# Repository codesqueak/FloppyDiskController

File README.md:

# Floppy Disk Controller Version 2.2.1

Nascom / Gemini / 80-Bus 1793 Floppy Disk Controller

## Introduction

This card has been designed to be a functional replacement for the Nascom Floppy Disk Controller.  It is fully compatible with the existing NAS-DOS software

The card is a completely new implementation of the design with a number of improvements over the original:

*	Completely new track layout
*	All components are readily available from commercial component suppliers (..and eBay!)
*	Switches are fitted to standard  DIL sockets
*	Copious test points
* Full documentation

For full documentation, see the [pdf here](FDC.pdf).

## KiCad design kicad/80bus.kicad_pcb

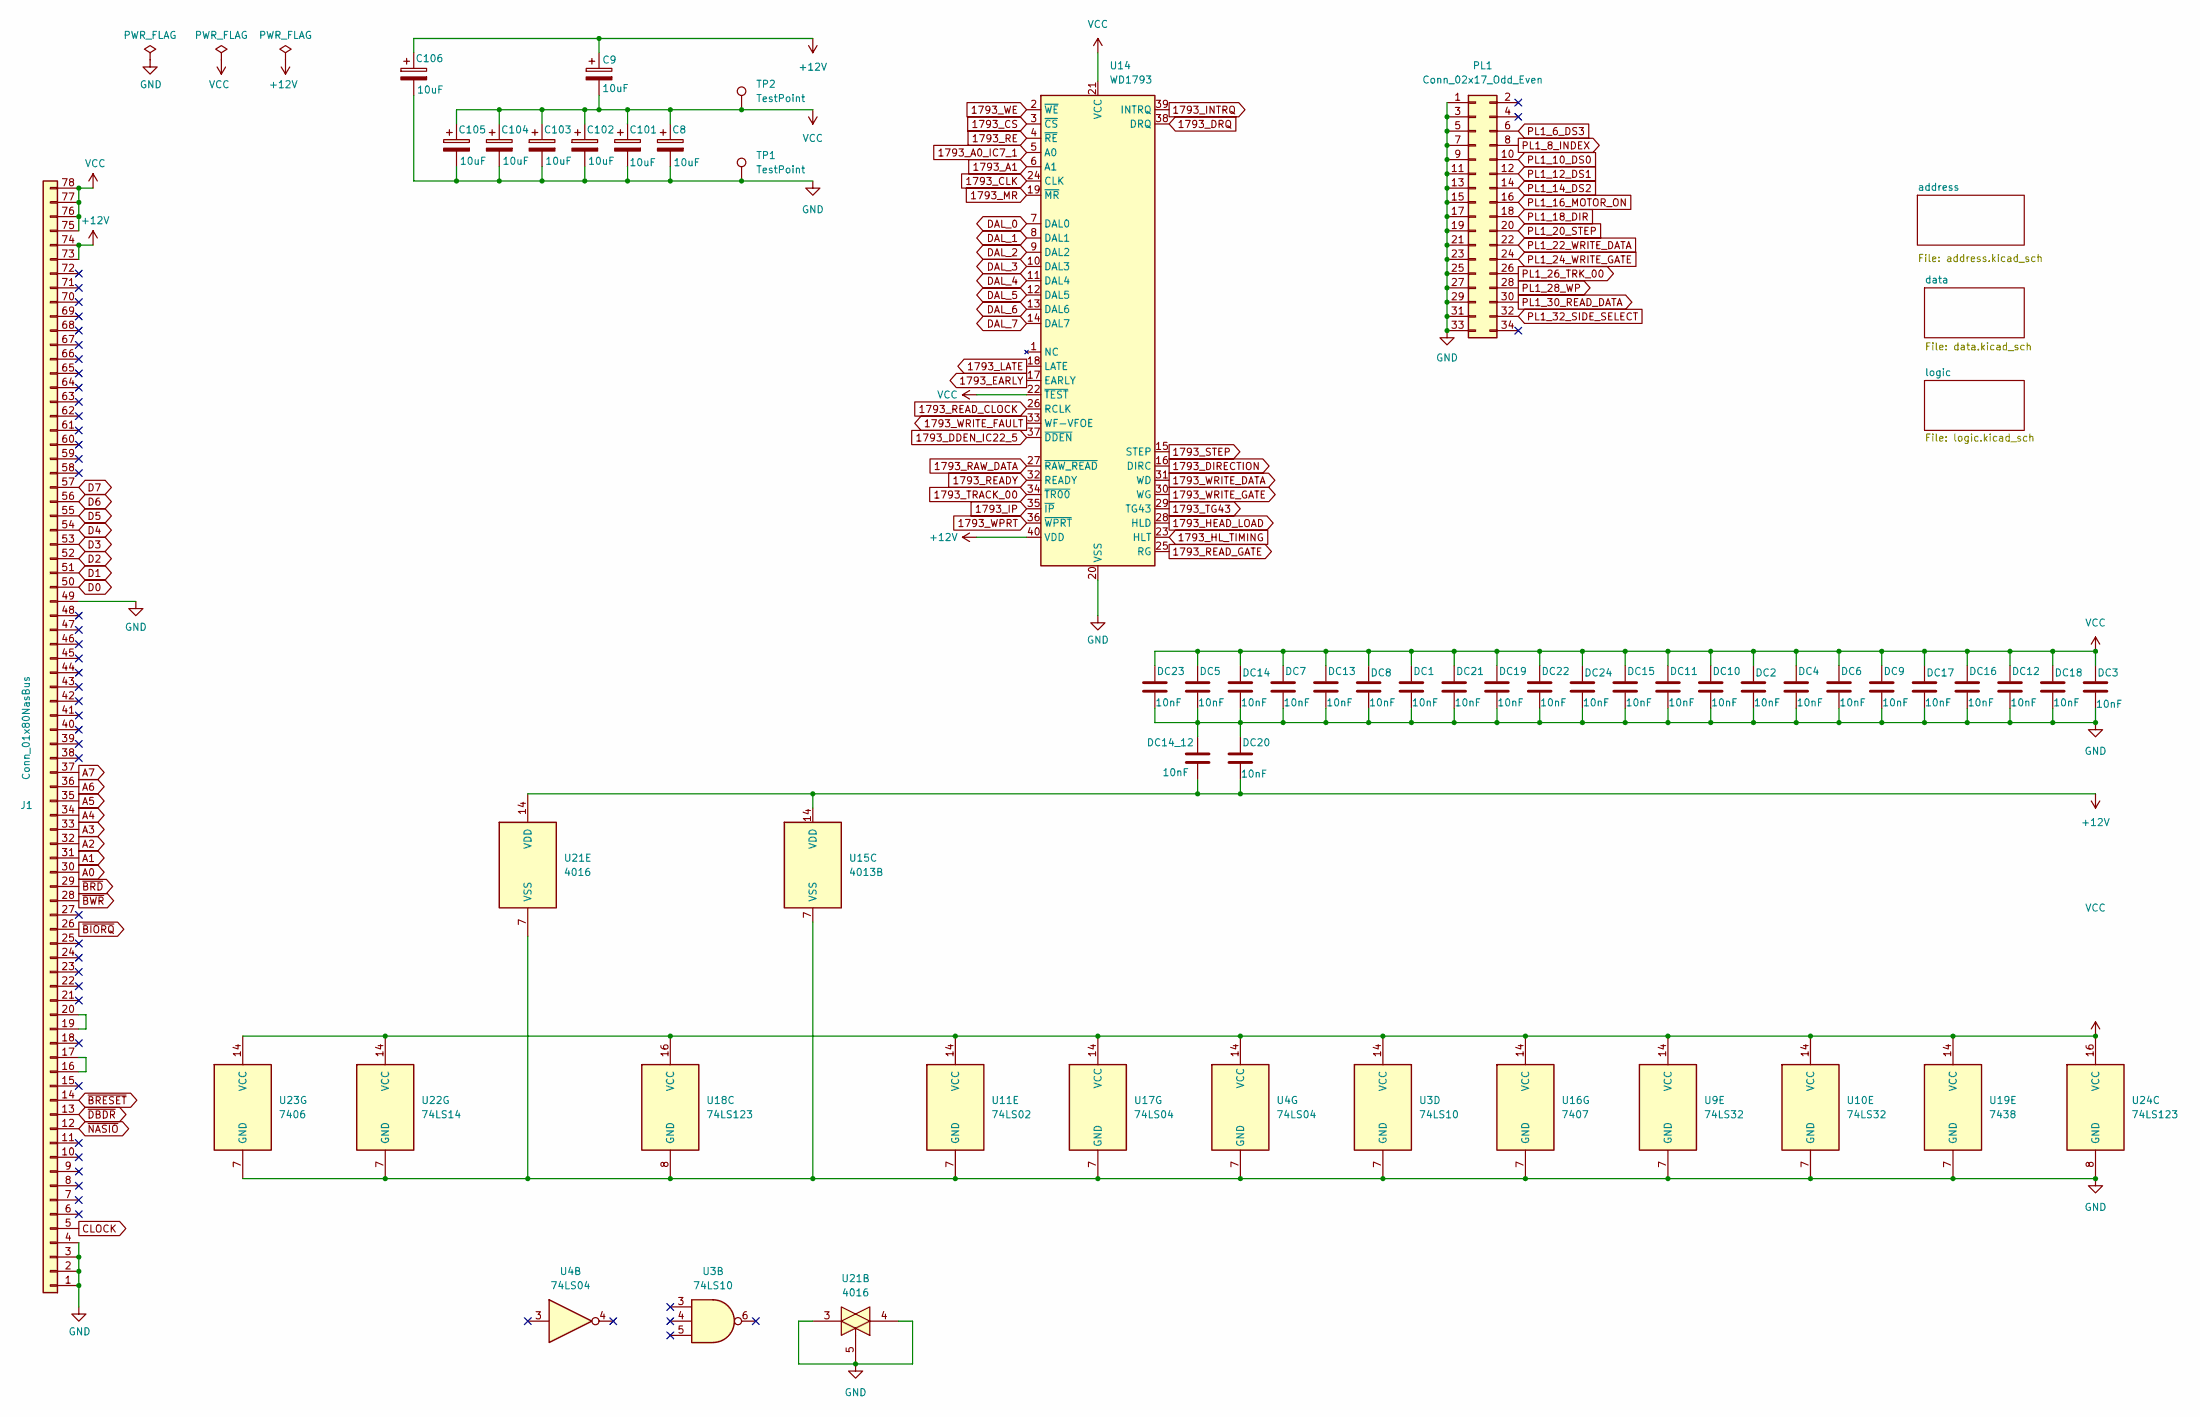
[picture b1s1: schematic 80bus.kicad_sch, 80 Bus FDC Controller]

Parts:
C8, C9, C101, C102, C103, C104, C105, C106: 10uF; C_Disc_D6.0mm_W4.4mm_P5.00mm
DC1, DC2, DC3, DC4, DC5, DC6, DC7, DC8, DC9, DC10, DC11, DC12, DC13, DC14, DC14_12, DC15, DC16, DC17, DC18, DC19, DC20, DC21, DC22, DC23, DC24: 10nF; C_Disc_D4.7mm_W2.5mm_P5.00mm
J1: Conn_01x80NasBus; 80BusEdgeConnector
PL1: Conn_02x17_Odd_Even; PinHeader_2x17_P2.54mm_Vertical
TP1, TP2: TestPoint; TestPoint_THTPad_D1.5mm_Drill0.7mm
U3: 74LS10; DIP-14_W7.62mm_Socket
U4, U17: 74LS04; DIP-14_W7.62mm_Socket
U9, U10: 74LS32; DIP-14_W7.62mm_Socket
U11: 74LS02; DIP-14_W7.62mm_Socket
U14: WD1793; DIP-40_W15.24mm
U15: 4013B; DIP-14_W7.62mm_Socket
U16: 7407; DIP-14_W7.62mm_Socket
U18, U24: 74LS123; DIP-16_W7.62mm_Socket
U19: 7438; DIP-14_W7.62mm_Socket
U21: 4016; DIP-14_W7.62mm_Socket
U22: 74LS14; DIP-14_W7.62mm_Socket
U23: 7406; DIP-14_W7.62mm_Socket

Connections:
1793_A0_IC7_1: U14.5 (A0); also elsewhere on the board
1793_A1: U14.6 (A1); also elsewhere on the board
1793_CLK: U14.24 (CLK); also elsewhere on the board
1793_CS: U14.3 (~CS); also elsewhere on the board
1793_DDEN_IC22_5: U14.37 (~DDEN); also elsewhere on the board
1793_DIRECTION: U14.16 (DIRC); also elsewhere on the board
1793_DRQ: U14.38 (DRQ); also elsewhere on the board
1793_EARLY: U14.17 (EARLY); also elsewhere on the board
1793_HEAD_LOAD: U14.28 (HLD); also elsewhere on the board
1793_HL_TIMING: U14.23 (HLT); also elsewhere on the board
1793_INTRQ: U14.39 (INTRQ); also elsewhere on the board
1793_IP: U14.35 (~IP); also elsewhere on the board
1793_LATE: U14.18 (LATE); also elsewhere on the board
1793_MR: U14.19 (~MR); also elsewhere on the board
1793_RAW_DATA: U14.27 (~RAW_READ); also elsewhere on the board
1793_RE: U14.4 (~RE); also elsewhere on the board
1793_READY: U14.32 (READY); also elsewhere on the board
1793_READ_CLOCK: U14.26 (RCLK); also elsewhere on the board
1793_READ_GATE: U14.25 (RG); also elsewhere on the board
1793_STEP: U14.15 (STEP); also elsewhere on the board
1793_TG43: U14.29 (TG43); also elsewhere on the board
1793_TRACK_00: U14.34 (~TR00); also elsewhere on the board
1793_WE: U14.2 (~WE); also elsewhere on the board
1793_WPRT: U14.36 (~WPRT); also elsewhere on the board
1793_WRITE_DATA: U14.31 (WD); also elsewhere on the board
1793_WRITE_FAULT: U14.33 (WF-VFOE); also elsewhere on the board
1793_WRITE_GATE: U14.30 (WG); also elsewhere on the board
+12V: C9.1, C106.1, DC14_12.2, DC20.2, J1.73 (Pin_73_+12v), J1.74 (Pin_74_+12v), U14.40 (VDD), U15.14 (VDD), U21.14 (VDD); also elsewhere on the board
A0: J1.30; also elsewhere on the board
A1: J1.31; also elsewhere on the board
A2: J1.32; also elsewhere on the board
A3: J1.33; also elsewhere on the board
A4: J1.34; also elsewhere on the board
A5: J1.35; also elsewhere on the board
A6: J1.36; also elsewhere on the board
A7: J1.37; also elsewhere on the board
CLOCK: J1.5; also elsewhere on the board
D0: J1.50; also elsewhere on the board
D1: J1.51; also elsewhere on the board
D2: J1.52; also elsewhere on the board
D3: J1.53; also elsewhere on the board
D4: J1.54; also elsewhere on the board
D5: J1.55; also elsewhere on the board
D6: J1.56; also elsewhere on the board
D7: J1.57; also elsewhere on the board
DAL_0: U14.7 (DAL0); also elsewhere on the board
DAL_1: U14.8 (DAL1); also elsewhere on the board
DAL_2: U14.9 (DAL2); also elsewhere on the board
DAL_3: U14.10 (DAL3); also elsewhere on the board
DAL_4: U14.11 (DAL4); also elsewhere on the board
DAL_5: U14.12 (DAL5); also elsewhere on the board
DAL_6: U14.13 (DAL6); also elsewhere on the board
DAL_7: U14.14 (DAL7); also elsewhere on the board
GND: C8.2, C101.2, C102.2, C103.2, C104.2, C105.2, C106.2, DC1.2, DC2.2, DC3.2, DC4.2, DC5.2, DC6.2, DC7.2, DC8.2, DC9.2, DC10.2, DC11.2, DC12.2, DC13.2, DC14.2, DC14_12.1, DC15.2, DC16.2, DC17.2, DC18.2, DC19.2, DC20.1, DC21.2, DC22.2, DC23.2, DC24.2, J1.1 (Pin_1_0v), J1.2 (Pin_2_0v), J1.3 (Pin_3_0v), J1.4 (Pin_4_0v), J1.49, PL1.1, PL1.3, PL1.5, PL1.7, PL1.9, PL1.11, PL1.13, PL1.15, PL1.17, PL1.19, PL1.21, PL1.23, PL1.25, PL1.27, PL1.29, PL1.31, PL1.33, TP1.1, U3.7 (GND), U4.7 (GND), U9.7 (GND), U10.7 (GND), U11.7 (GND), U14.20 (VSS), U15.7 (VSS), U16.7 (GND), U17.7 (GND), U18.8 (GND), U19.7 (GND), U21.3, U21.4, U21.5, U21.7 (VSS), U22.7 (GND), U23.7 (GND), U24.8 (GND); also elsewhere on the board
unnamed: J1.16, J1.17
unnamed: J1.19, J1.20
PL1_6_DS3: PL1.6; also elsewhere on the board
PL1_8_INDEX: PL1.8; also elsewhere on the board
PL1_10_DS0: PL1.10; also elsewhere on the board
PL1_12_DS1: PL1.12; also elsewhere on the board
PL1_14_DS2: PL1.14; also elsewhere on the board
PL1_16_MOTOR_ON: PL1.16; also elsewhere on the board
PL1_18_DIR: PL1.18; also elsewhere on the board
PL1_20_STEP: PL1.20; also elsewhere on the board
PL1_22_WRITE_DATA: PL1.22; also elsewhere on the board
PL1_24_WRITE_GATE: PL1.24; also elsewhere on the board
PL1_26_TRK_00: PL1.26; also elsewhere on the board
PL1_28_WP: PL1.28; also elsewhere on the board
PL1_30_READ_DATA: PL1.30; also elsewhere on the board
PL1_32_SIDE_SELECT: PL1.32; also elsewhere on the board
VCC: C8.1, C9.2, C101.1, C102.1, C103.1, C104.1, C105.1, DC1.1, DC2.1, DC3.1, DC4.1, DC5.1, DC6.1, DC7.1, DC8.1, DC9.1, DC10.1, DC11.1, DC12.1, DC13.1, DC14.1, DC15.1, DC16.1, DC17.1, DC18.1, DC19.1, DC21.1, DC22.1, DC23.1, DC24.1, J1.75 (Pin_75_+5v), J1.76 (Pin_76_+5v), J1.77 (Pin_77__+5v), J1.78 (Pin_78__+5v), TP2.1, U3.14 (VCC), U4.14 (VCC), U9.14 (VCC), U10.14 (VCC), U11.14 (VCC), U14.21 (VCC), U14.22 (~TEST), U16.14 (VCC), U17.14 (VCC), U18.16 (VCC), U19.14 (VCC), U22.14 (VCC), U23.14 (VCC), U24.16 (VCC); also elsewhere on the board
~BIORQ: J1.26; also elsewhere on the board
~BRD: J1.29; also elsewhere on the board
~BRESET: J1.14; also elsewhere on the board
~BWR: J1.28; also elsewhere on the board
~DBDR: J1.13; also elsewhere on the board
~NASIO: J1.12; also elsewhere on the board

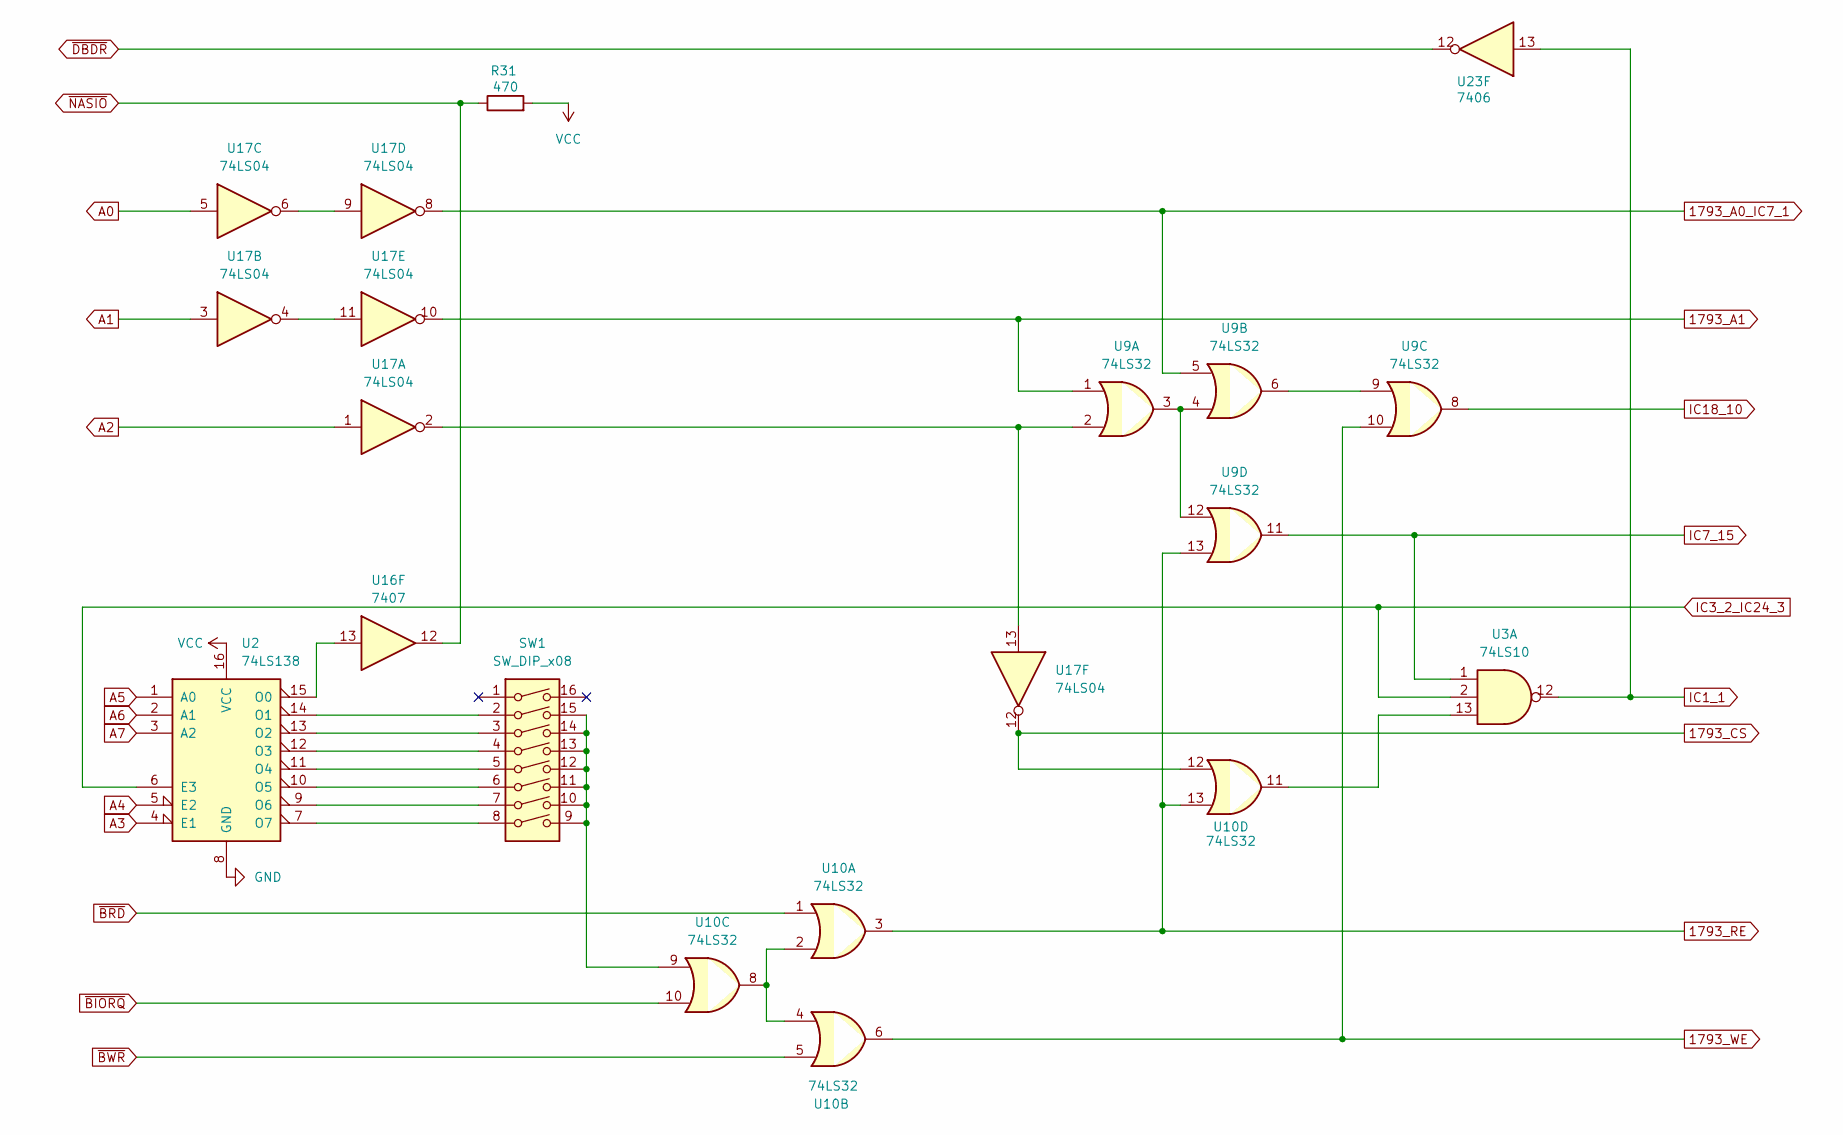
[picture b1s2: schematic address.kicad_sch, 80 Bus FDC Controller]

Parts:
R31: 470; R_Axial_DIN0309_L9.0mm_D3.2mm_P12.70mm_Horizontal
SW1: SW_DIP_x08; DIP-16_W7.62mm_Socket
U2: 74LS138; DIP-16_W7.62mm_Socket
U3: 74LS10; DIP-14_W7.62mm_Socket
U9, U10: 74LS32; DIP-14_W7.62mm_Socket
U16: 7407; DIP-14_W7.62mm_Socket
U17: 74LS04; DIP-14_W7.62mm_Socket
U23: 7406; DIP-14_W7.62mm_Socket

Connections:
1793_A0_IC7_1: U9.5, U17.8; also elsewhere on the board
1793_A1: U9.1, U17.10; also elsewhere on the board
1793_CS: U10.12, U17.12; also elsewhere on the board
1793_RE: U9.13, U10.3, U10.13; also elsewhere on the board
1793_WE: U9.10, U10.6; also elsewhere on the board
A0: U17.5; also elsewhere on the board
A1: U17.3; also elsewhere on the board
A2: U17.1; also elsewhere on the board
A3: U2.4 (E1); also elsewhere on the board
A4: U2.5 (E2); also elsewhere on the board
A5: U2.1 (A0); also elsewhere on the board
A6: U2.2 (A1); also elsewhere on the board
A7: U2.3 (A2); also elsewhere on the board
GND: U2.8 (GND); also elsewhere on the board
IC1_1: U3.12, U23.13; also elsewhere on the board
IC3_2_IC24_3: U2.6 (E3), U3.2; also elsewhere on the board
IC7_15: U3.1, U9.11; also elsewhere on the board
IC18_10: U9.8; also elsewhere on the board
unnamed: SW1.9, SW1.10, SW1.11, SW1.12, SW1.13, SW1.14, SW1.15, U10.9
unnamed: U2.15 (O0), U16.13
unnamed: SW1.2, U2.14 (O1)
unnamed: SW1.3, U2.13 (O2)
unnamed: SW1.4, U2.12 (O3)
unnamed: SW1.5, U2.11 (O4)
unnamed: SW1.6, U2.10 (O5)
unnamed: SW1.7, U2.9 (O6)
unnamed: SW1.8, U2.7 (O7)
unnamed: U9.6, U9.9
unnamed: U9.3, U9.4, U9.12
unnamed: U10.2, U10.4, U10.8
unnamed: U3.13, U10.11
unnamed: U17.6, U17.9
unnamed: U17.4, U17.11
unnamed: U9.2, U17.2, U17.13
VCC: R31.2, U2.16 (VCC); also elsewhere on the board
~BIORQ: U10.10; also elsewhere on the board
~BRD: U10.1; also elsewhere on the board
~BWR: U10.5; also elsewhere on the board
~DBDR: U23.12; also elsewhere on the board
~NASIO: R31.1, U16.12; also elsewhere on the board

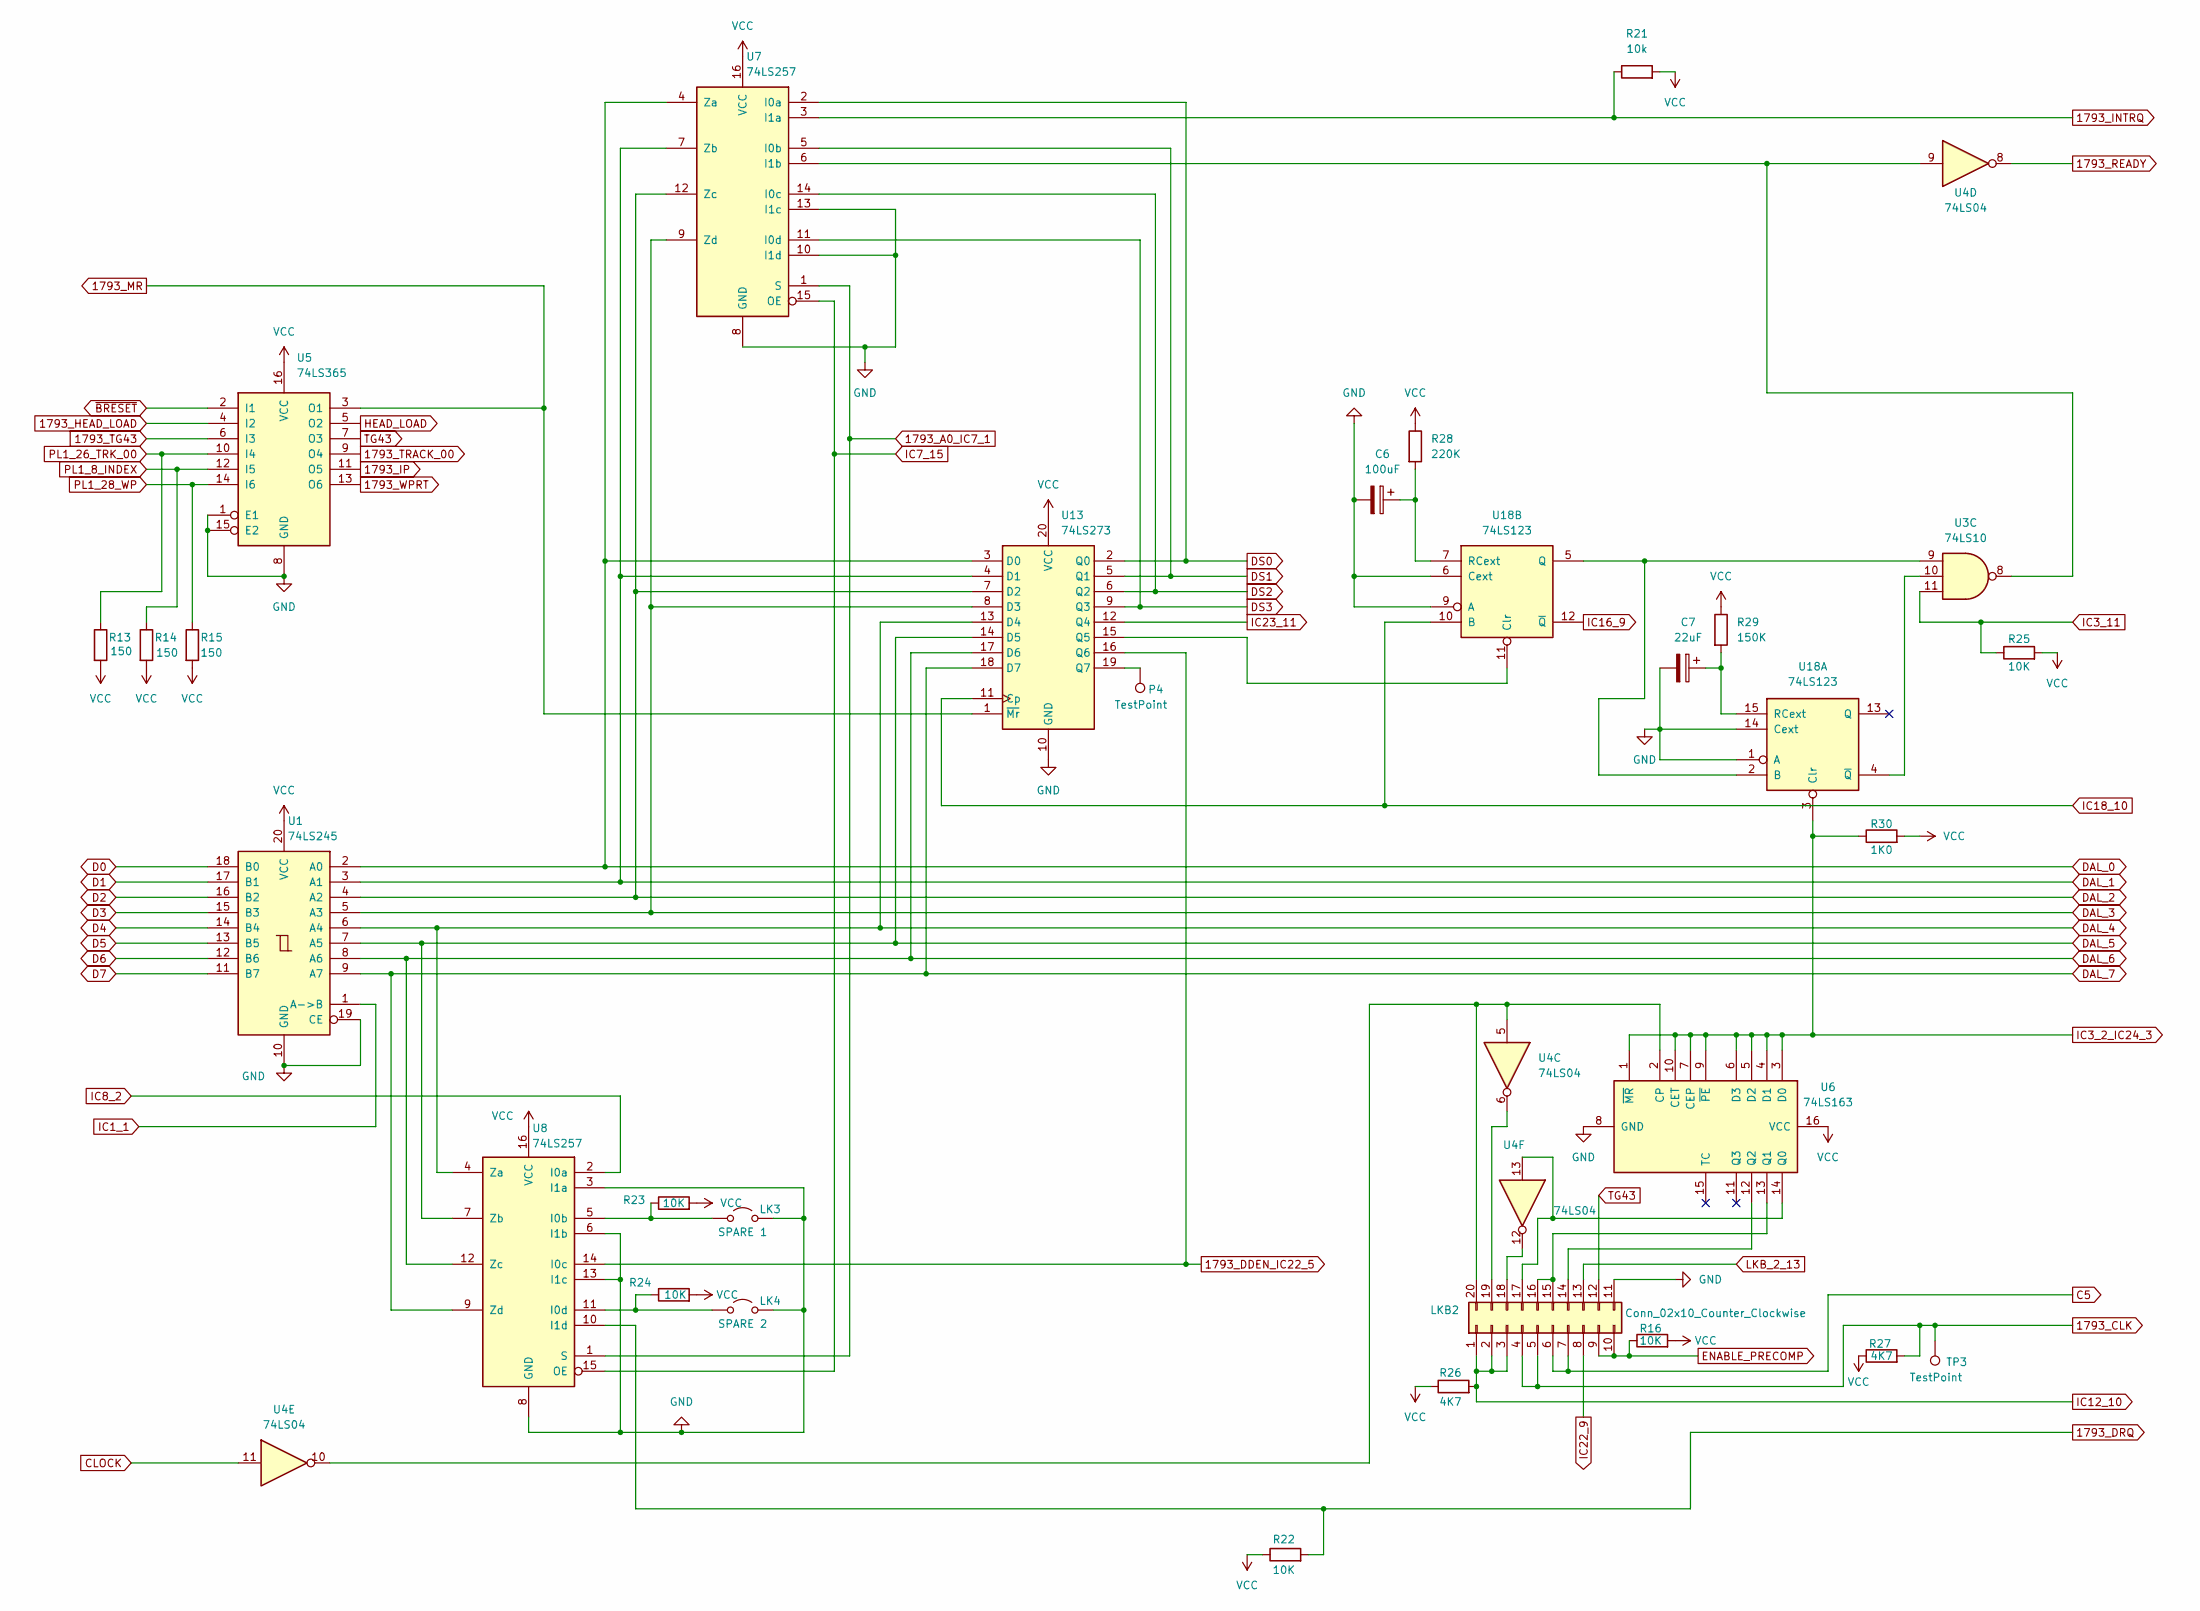
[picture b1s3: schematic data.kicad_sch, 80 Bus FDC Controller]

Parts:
C6: 100uF; C_Disc_D6.0mm_W4.4mm_P5.00mm
C7: 22uF; C_Disc_D6.0mm_W4.4mm_P5.00mm
LK3: SPARE 1; SW_DIP_SPSTx01_Slide_6.7x4.1mm_W7.62mm_P2.54mm_LowProfile
LK4: SPARE 2; SW_DIP_SPSTx01_Slide_6.7x4.1mm_W7.62mm_P2.54mm_LowProfile
LKB2: Conn_02x10_Counter_Clockwise; DIP-20_W7.62mm_Socket
P4: TestPoint; TestPoint_THTPad_D1.5mm_Drill0.7mm
R13, R14, R15: 150; R_Axial_DIN0309_L9.0mm_D3.2mm_P12.70mm_Horizontal
R16, R22, R23, R24, R25: 10K; R_Axial_DIN0309_L9.0mm_D3.2mm_P12.70mm_Horizontal
R21: 10k; R_Axial_DIN0309_L9.0mm_D3.2mm_P12.70mm_Horizontal
R26, R27: 4K7; R_Axial_DIN0309_L9.0mm_D3.2mm_P12.70mm_Horizontal
R28: 220K; R_Axial_DIN0309_L9.0mm_D3.2mm_P12.70mm_Horizontal
R29: 150K; R_Axial_DIN0309_L9.0mm_D3.2mm_P12.70mm_Horizontal
R30: 1K0; R_Axial_DIN0309_L9.0mm_D3.2mm_P12.70mm_Horizontal
TP3: TestPoint; TestPoint_THTPad_D1.5mm_Drill0.7mm
U1: 74LS245; DIP-20_W7.62mm_Socket
U3: 74LS10; DIP-14_W7.62mm_Socket
U4: 74LS04; DIP-14_W7.62mm_Socket
U5: 74LS365; DIP-16_W7.62mm_Socket
U6: 74LS163; DIP-16_W7.62mm_Socket
U7, U8: 74LS257; DIP-16_W7.62mm_Socket
U13: 74LS273; DIP-20_W7.62mm_Socket
U18: 74LS123; DIP-16_W7.62mm_Socket

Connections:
1793_A0_IC7_1: U7.1 (S), U8.1 (S); also elsewhere on the board
1793_CLK: LKB2.4, LKB2.5, R27.2, TP3.1; also elsewhere on the board
1793_DDEN_IC22_5: U8.14 (I0c), U13.16 (Q6); also elsewhere on the board
1793_DRQ: R22.2, U8.10 (I1d); also elsewhere on the board
1793_HEAD_LOAD: U5.4 (I2); also elsewhere on the board
1793_INTRQ: R21.1, U7.3 (I1a); also elsewhere on the board
1793_IP: U5.11 (O5); also elsewhere on the board
1793_MR: U5.3 (O1), U13.1 (~Mr); also elsewhere on the board
1793_READY: U4.8; also elsewhere on the board
1793_TG43: U5.6 (I3); also elsewhere on the board
1793_TRACK_00: U5.9 (O4); also elsewhere on the board
1793_WPRT: U5.13 (O6); also elsewhere on the board
C5: LKB2.6, LKB2.7; also elsewhere on the board
CLOCK: U4.11; also elsewhere on the board
D0: U1.18 (B0); also elsewhere on the board
D1: U1.17 (B1); also elsewhere on the board
D2: U1.16 (B2); also elsewhere on the board
D3: U1.15 (B3); also elsewhere on the board
D4: U1.14 (B4); also elsewhere on the board
D5: U1.13 (B5); also elsewhere on the board
D6: U1.12 (B6); also elsewhere on the board
D7: U1.11 (B7); also elsewhere on the board
DAL_0: U1.2 (A0), U7.4 (Za), U13.3 (D0); also elsewhere on the board
DAL_1: U1.3 (A1), U7.7 (Zb), U13.4 (D1); also elsewhere on the board
DAL_2: U1.4 (A2), U7.12 (Zc), U13.7 (D2); also elsewhere on the board
DAL_3: U1.5 (A3), U7.9 (Zd), U13.8 (D3); also elsewhere on the board
DAL_4: U1.6 (A4), U8.4 (Za), U13.13 (D4); also elsewhere on the board
DAL_5: U1.7 (A5), U8.7 (Zb), U13.14 (D5); also elsewhere on the board
DAL_6: U1.8 (A6), U8.12 (Zc), U13.17 (D6); also elsewhere on the board
DAL_7: U1.9 (A7), U8.9 (Zd), U13.18 (D7); also elsewhere on the board
DS0: U7.2 (I0a), U13.2 (Q0); also elsewhere on the board
DS1: U7.5 (I0b), U13.5 (Q1); also elsewhere on the board
DS2: U7.14 (I0c), U13.6 (Q2); also elsewhere on the board
DS3: U7.11 (I0d), U13.9 (Q3); also elsewhere on the board
ENABLE_PRECOMP: LKB2.9, LKB2.10, R16.1; also elsewhere on the board
GND: C6.2, C7.2, LK3.2 (B), LK4.2 (B), LKB2.11, U1.10 (GND), U1.19 (CE), U5.1 (E1), U5.8 (GND), U5.15 (E2), U6.8 (GND), U7.8 (GND), U7.10 (I1d), U7.13 (I1c), U8.3 (I1a), U8.6 (I1b), U8.8 (GND), U8.13 (I1c), U13.10 (GND), U18.1 (A), U18.6 (Cext), U18.9 (A), U18.14 (Cext); also elsewhere on the board
HEAD_LOAD: U5.5 (O2); also elsewhere on the board
IC1_1: U1.1 (A->B); also elsewhere on the board
IC3_2_IC24_3: R30.1, U6.1 (~MR), U6.3 (D0), U6.4 (D1), U6.5 (D2), U6.6 (D3), U6.7 (CEP), U6.9 (~PE), U6.10 (CET), U18.3 (Clr); also elsewhere on the board
IC3_11: R25.1, U3.11; also elsewhere on the board
IC7_15: U7.15 (OE), U8.15 (OE); also elsewhere on the board
IC8_2: U8.2 (I0a); also elsewhere on the board
IC12_10: LKB2.1, LKB2.2, LKB2.3, R26.2; also elsewhere on the board
IC16_9: U18.12 (~Q); also elsewhere on the board
IC18_10: U13.11 (Cp), U18.10 (B); also elsewhere on the board
IC22_9: LKB2.8; also elsewhere on the board
IC23_11: U13.12 (Q4); also elsewhere on the board
LKB_2_13: LKB2.13; also elsewhere on the board
unnamed: LK3.1 (A), R23.1, U8.5 (I0b)
unnamed: LK4.1 (A), R24.1, U8.11 (I0d)
unnamed: LKB2.14, U6.12 (Q2)
unnamed: LKB2.15, LKB2.16, U6.13 (Q1)
unnamed: LKB2.17, U4.13, U6.14 (Q0)
unnamed: LKB2.18, U4.12
unnamed: LKB2.19, U4.6
unnamed: LKB2.20, U4.5, U4.10, U6.2 (CP)
unnamed: U3.8, U4.9, U7.6 (I1b)
unnamed: U13.15 (Q5), U18.11 (Clr)
unnamed: P4.1, U13.19 (Q7)
unnamed: U3.9, U18.2 (B), U18.5 (Q)
unnamed: C7.1, R29.2, U18.15 (RCext)
unnamed: U3.10, U18.4 (~Q)
unnamed: C6.1, R28.2, U18.7 (RCext)
PL1_8_INDEX: R14.1, U5.12 (I5); also elsewhere on the board
PL1_26_TRK_00: R13.1, U5.10 (I4); also elsewhere on the board
PL1_28_WP: R15.1, U5.14 (I6); also elsewhere on the board
TG43: LKB2.12, U5.7 (O3); also elsewhere on the board
VCC: R13.2, R14.2, R15.2, R16.2, R21.2, R22.1, R23.2, R24.2, R25.2, R26.1, R27.1, R28.1, R29.1, R30.2, U1.20 (VCC), U5.16 (VCC), U6.16 (VCC), U7.16 (VCC), U8.16 (VCC), U13.20 (VCC); also elsewhere on the board
~BRESET: U5.2 (I1); also elsewhere on the board
